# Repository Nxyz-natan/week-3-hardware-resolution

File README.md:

# week-3-hardware-resolution
# NE555 LED Blinker

A PCB that uses a NE555P timer IC in astable mode to automatically 
blink an LED on and off The timing is controlled by resistors and 
a capacitor connected to the 555 timer

PCB Render

## How it works

The NE555P runs in astable mode generating a continuous square wave 
signal The frequency is determined by R4 (10k) R5 (1k), and C1 (10uF) 
A 470Ω resistor (R6) limits current to the LED to prevent it from burning out

KiCanvas Link: https://kicanvas.org/?repo=https%3A%2F%2Fgithub.com%2FNxyz-natan%2Fweek-3-hardware-resolution%2Ftree%2Fmain%2Fsrc

## Schematic

Schematic: 

## PCB

PCB:

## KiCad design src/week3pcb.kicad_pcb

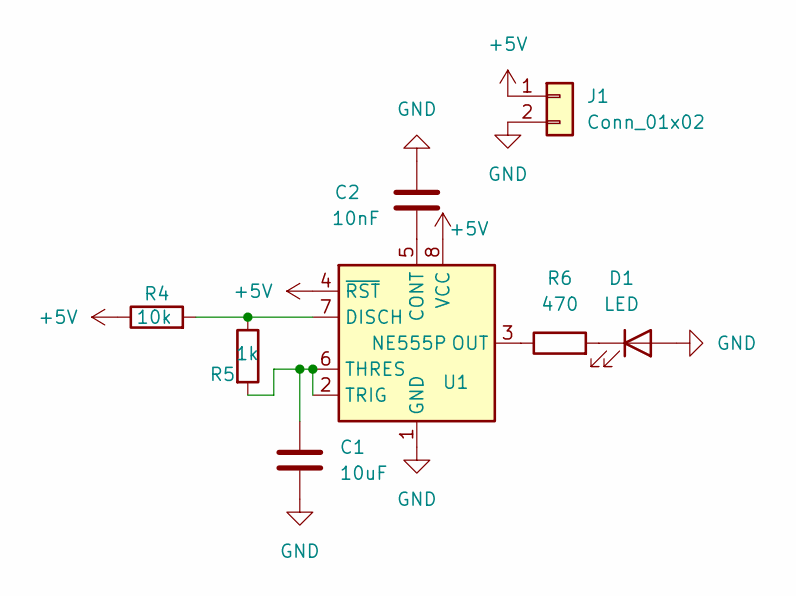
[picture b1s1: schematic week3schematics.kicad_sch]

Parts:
C1: 10uF; C_Disc_D5.0mm_W2.5mm_P5.00mm
C2: 10nF; C_Disc_D5.0mm_W2.5mm_P5.00mm
D1: LED; LED_D5.0mm
J1: Conn_01x02; PinHeader_1x02_P2.54mm_Vertical
R4: 10k; R_Axial_DIN0204_L3.6mm_D1.6mm_P7.62mm_Horizontal
R5: 1k; R_Axial_DIN0204_L3.6mm_D1.6mm_P7.62mm_Horizontal
R6: 470; R_Axial_DIN0204_L3.6mm_D1.6mm_P7.62mm_Horizontal
U1: NE555P; DIP-8_W7.62mm

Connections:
+5V: J1.1, R4.1, U1.4 (~RST), U1.8 (VCC)
GND: C1.1, C2.2, D1.2 (A), J1.2, U1.1 (GND)
unnamed: D1.1 (K), R6.2
unnamed: C2.1, U1.5 (CONT)
unnamed: R4.2, R5.1, U1.7 (DISCH)
unnamed: R6.1, U1.3 (OUT)
unnamed: C1.2, R5.2, U1.2 (TRIG), U1.6 (THRES)

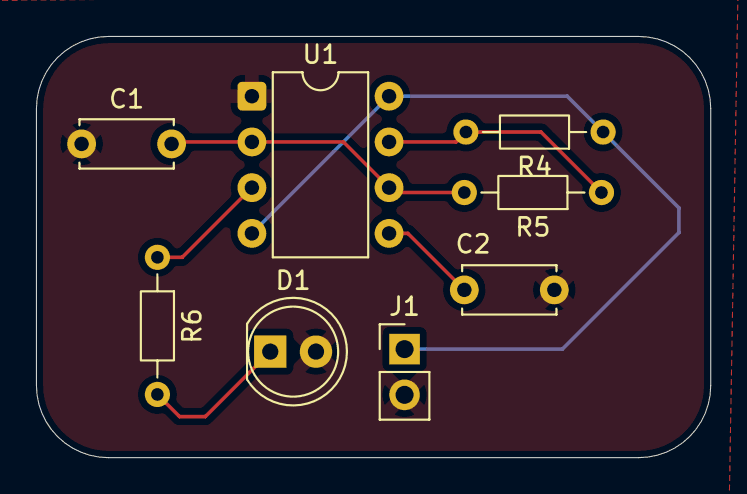
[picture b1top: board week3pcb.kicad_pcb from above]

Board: 2 copper layers, 37.5 x 23.4 mm, 8 parts (0 on the bottom side), 7 nets.

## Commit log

2026-05-26 Document NE555 LED blinker project in README
    Added project details for NE555 LED blinker, including schematic design and PCB routing.
2026-05-30 Add journal entry for NE555 LED blinker project
    Document progress on NE555 LED blinker project, including schematic design and PCB routing.
